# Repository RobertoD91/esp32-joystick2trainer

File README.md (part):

# esp32-joystick2trainer

> ⚠️ **AI-generated code.** This project (firmware, tests, CI and documentation) was written by
> an AI model, **Claude Fable 5.1** running in Claude Code, from a human specification and with
> human review and bench testing. Read the code before trusting it with anything that flies, and
> report anything odd in the issues.

*Click the image to watch the demo on YouTube.*

Firmware for the **ESP32-S3** that turns a wired **USB HID joystick** into a trainer input for
**EdgeTX** radios such as the **RadioMaster TX16S MKII**. The ESP32-S3 acts as a native USB host,
decodes the joystick's HID reports and emits **SBUS** and **CPPM** at the same time on two GPIOs.

```text
USB HID joystick  (e.g. Microsoft SideWinder Force Feedback 2, 045E:001B)
      │  USB full speed
      ▼
ESP32-S3 native USB host  ──►  HID report descriptor parser  ──►  normalised axes/buttons/hat
      │
      ▼
configurable channel mapping (source, invert, dead band, expo, end points, trim, failsafe)
      ├──►  SBUS  (UART1, 100000 8E2, hardware inverted)  ──►  GPIO 17
      └──►  CPPM  (RMT peripheral, no bit-banging)        ──►  GPIO 18
```

Force feedback is used for one thing: the bridge creates the **centring spring** on the joystick
(a USB HID PID effect; without it a SideWinder is loose) and offers a vibration test. Game-style
effects are out of scope.

> **Status:** flown. The firmware at commit `59b4e3c` (release v0.9.0 plus documentation
> updates) was used for a **first real flight on 2026-10-24** with a SideWinder Force Feedback 2,
> an ESP32-S3-DevKitC-1 and a RadioMaster TX16S MKII running EdgeTX, SBUS on the radio's AUX
> serial port (`Master/Serial`): it worked without issues. The CPPM output on the trainer jack
> and the SBUS input on the module bay S.PORT pin are implemented but **not yet tested on the
> radio**, and the force feedback added afterwards still needs its first bench test. See
> [Tested setups](#tested-setups).

## Contents

- [Features](#features)
- [Hardware](#hardware)
- [Wiring to the TX16S MKII](#wiring-to-the-tx16s-mkii)
- [EdgeTX setup](#edgetx-setup)
- [Building, flashing, testing](#building-flashing-testing)
- [Configuration](#configuration)
- [Architecture](#architecture)
- [Design decisions](#design-decisions)
- [Limitations and roadmap](#limitations-and-roadmap)

## Features

- **Native USB host** on the ESP32-S3 (ESP-IDF `usb` host library + Espressif `usb_host_hid`
  class driver). No Bluetooth, no external USB host shield.
- **Force feedback centring spring** for USB HID PID joysticks (SideWinder Force Feedback 2):
  the stick returns to centre by itself; strength and gain are configurable, plus a vibration
  test.
- **Generic HID joystick support**: the report descriptor is parsed at run time, so any joystick
  or gamepad that follows the HID usage tables works (X/Y/Z/Rx/Ry/Rz/slider/dial/wheel,
  throttle/rudder/accelerator/brake, hat switch, up to 32 buttons, report IDs, array buttons).
  The SideWinder Force Feedback 2 descriptor is part of the test suite.
- **SBUS and CPPM simultaneously**, each on its own GPIO, each individually configurable
  (period, polarity, number of channels, pulse width, frame length).
- **CPPM generated by the RMT peripheral**: the whole frame is handed to the hardware, timing does
  not depend on interrupt latency or on the USB task.
- **SBUS inversion in hardware** (UART TX inverter of the ESP32): no external transistor.
- **Safe disconnection handling**: on USB unplug the outputs go to a configurable failsafe
  (stop, hold, preset). By default they simply stop, which makes EdgeTX hand control back to
  the instructor's sticks within one second.
- **Everything configurable at run time** from a serial console and persisted in NVS:
  GPIOs, mapping per channel, inversion, dead band, expo, end points, trims, failsafe values,
  timings. Compile-time defaults are `-D` flags in `platformio.ini`.
- **PlatformIO project** with host-side unit tests (`pio test -e native`) and a GitHub Actions
  pipeline (format check, tests, firmware build with downloadable artifacts).

## Hardware

### Bill of materials

| Item | Notes |
|------|-------|
| ESP32-S3 dev board | Tested build target: `esp32-s3-devkitc-1`. Any ESP32-S3 board that exposes the **native USB** pins (GPIO19/20) works. Other chips: see [docs/hardware-options.md](docs/hardware-options.md) (short version: ESP32-S2 yes, RP2040/RP2350 and ESP32-C3/C5 no). |
| JR bay module (prototype PCB) | A 22 x 62 mm board that plugs into the radio's module bay: ESP32-S3-WROOM-1, USB-A host port, USB-C console, 2S buck, SBUS/CPPM on the bay pins and an AUX header. KiCad project, Gerbers, BOM and a printable case in [hardware/](hardware/README.md). Untested as of this release. |
| USB OTG cable **with power input** | Micro-USB (USB-C on some boards) OTG host plug + USB-A female for the joystick + a power input. See [Powering the joystick](#powering-the-joystick): a plain OTG adapter is not enough on the DevKitC-1. |
| USB-to-UART link | The DevKitC-1's second connector labelled "UART"; used for flashing, logs and the configuration console. |
| 3.5 mm TRS plug | For the CPPM trainer input of the radio. |
| Dupont wires / JR pins | For the SBUS input (module bay S.PORT pin or AUX serial connector). |

### Powering the joystick

The joystick must receive **5 V on VBUS** from the host connector, and the
**ESP32-S3-DevKitC-1 cannot provide it by design**: in the board schematic the VBUS pin of the
native "USB" connector (J4) reaches the 5 V rail only through the Schottky diode D7, oriented
from the connector *into* the board. The board can be powered from that port, but 5 V never
flows out to a connected device, and there is no jumper or solder pad to change that. The
firmware therefore enumerates nothing until VBUS is supplied in one of these ways:

1. **OTG Y-cable with power input** (no soldering, recommended): a "micro-USB OTG host + power"
   cable. Its power socket takes 5 V from a USB charger, its USB-A socket feeds the joystick, and
   the same 5 V also enters the board through D7, so one supply powers everything while the
   UART port stays free for the console.
2. **Wire from the header pin `5V` to the VBUS pad of J4**, or a solder bridge across D7. The
   board is then powered from the UART port or the `5V` pin. With D7 bridged, never connect a
   PC to the native port while the board is powered from another source.
3. **USB-A female breakout on the header**: VBUS to `5V`, GND to `GND`, D+ to `GPIO20`, D- to
   `GPIO19`, short twisted wires; the on-board connector is left unused.

The SideWinder FFB2 declares 100 mA over USB; it also has its own mains power supply for the
motors, which must be connected for the stick to enumerate reliably.

Power the ESP32 from its UART/USB connector or from a clean 5 V source. **Do not** power it from
the radio's module bay `BATT` pin: that pin carries the battery voltage (up to 8.4 V).

### GPIO usage (defaults)

| Signal | GPIO | Level | Change with |
|--------|------|-------|-------------|
| SBUS out | 17 | 3.3 V, idle low (inverted UART, standard SBUS) | `set sbus.gpio N`, `set sbus.inverted 0/1` |
| CPPM out | 18 | 3.3 V, idle high, 300 µs low pulses | `set cppm.gpio N`, `set cppm.inverted 0/1` |
| Status LED | none (-1) | active high | `set led.gpio N` |
| USB host D-/D+ | 19 / 20 | native USB | fixed |
| Console | UART0 (USB-UART bridge) | 115200 8N1 | fixed |

Avoid the strapping pins (0, 3, 45, 46), the flash/PSRAM pins (26-37 on modules with octal
PSRAM) and 19/20 (USB). 3.3 V logic is enough for the STM32 inputs of the TX16S (they are 5 V
tolerant, threshold about 2 V).

## Wiring to the TX16S MKII

EdgeTX offers several trainer input modes. The ones usable with this bridge on a TX16S are:

| EdgeTX trainer mode | Physical input on the TX16S | Signal to send | Bridge setting |
|---------------------|-----------------------------|----------------|----------------|
| **Master/Jack** | 3.5 mm trainer jack on the back | CPPM | `cppm.*` defaults |
| **Master/SBUS Module** | external module bay, **S.PORT** pin (with External RF **off**) | SBUS, standard polarity (idle low) | `sbus.inverted 1` (default) |
| **Master/Serial** | AUX1 (or AUX2) serial port configured as "SBUS Trainer" | SBUS, **UART polarity** (idle high) | `sbus.inverted 0` |
| Master/CPPM Module | module bay HEARTBEAT pin | – | **does not work on the TX16S/MKII** (hardware issue, EdgeTX issue #4672) |

EdgeTX uses one trainer mode per model, so in practice you connect **either** the CPPM output
**or** the SBUS output to the radio. Both are generated all the time; the other one is free for a
second radio or a simulator dongle.

### Tested setups

| Path | Radio side | Bridge side | Result |
|------|-----------|-------------|--------|
| **SBUS on AUX serial port** | TX16S MKII, EdgeTX, AUX port on the bottom set to `SBUS Trainer`, model in `Master/Serial`; external bay occupied by an ExpressLRS module, internal multi-protocol module | GPIO17 → AUX RX, GND → GND, **`set sbus.inverted 0`** + `save` | **Works, flown.** Bench-verified on 2026-09-20, first flight on 2026-10-24 with the firmware of commit `59b4e3c`: the model was flown from the joystick through the trainer function without any issue. |
| CPPM on the trainer jack | `Master/Jack` | GPIO18 → tip, GND → sleeve | Not yet tested (no jack at hand). Encoder timing is covered by unit tests against EdgeTX's decoder rules. |
| SBUS on module bay S.PORT | `Master/SBUS Module`, External RF off | GPIO17 → pin 5, `sbus.inverted 1` | Not yet tested (bay occupied by the ELRS module). |
| Force feedback (centring spring) | – | SideWinder FFB2 with its mains adapter connected | Implemented after the first flight, **not yet bench-tested**: the report sequence is verified against the real descriptor in the unit tests only. See [Force feedback](#force-feedback). |

Lessons learned during the first bring-up:

- The DevKitC-1 does not power the joystick from its native USB port; a powered OTG Y-cable
  fixed it (see [Powering the joystick](#powering-the-joystick)).
- The **AUX port wants UART polarity**: with the default `sbus.inverted 1` the radio sees
  nothing at all. `set sbus.inverted 0` takes effect immediately, then `save`.
- With the default `failsafe.mode stop` nothing is emitted until the joystick sends its first
  report; the SideWinder only reports on change, so move the stick once and check `status`.

### CPPM on the trainer jack (not yet verified on the radio)

```text
ESP32-S3 GPIO18 ──────► tip    (PPM)      3.5 mm TRS plug
ESP32-S3 GND    ──────► sleeve (GND)
                        ring   not connected
```

This follows the OpenTX/EdgeTX convention (PPM on the tip, ground on the sleeve, ring unused).
The original TX16S used a 4-pole socket, the MKII a standard 3-pole TRS socket. If your radio
does not see the signal, verify the socket with a multimeter (sleeve = ground) before assuming
a firmware problem. EdgeTX measures rising edge to rising edge, accepts 800-2200 µs per channel
and needs a sync gap of 4-19 ms; the encoder keeps every frame inside that window by design.

### SBUS on the module bay (S.PORT pin)

```text
JR module bay (top to bottom):  1 PPM   2 HEARTBEAT   3 BATT   4 GND   5 S.PORT
ESP32-S3 GPIO17 ──────► pin 5 (S.PORT)
ESP32-S3 GND    ──────► pin 4 (GND)
```

Keep `sbus.inverted = 1` (standard SBUS). Set the model's External RF to **OFF** or the mode is
not offered. Never connect pin 3 (BATT) to the ESP32.

### SBUS on the AUX serial port (verified)

```text
ESP32-S3 GPIO17 ──────► AUX port RX pin (the radio's receive line)
ESP32-S3 GND    ──────► AUX port GND
                        AUX port 5V and TX left unconnected
```

Set **`sbus.inverted = 0`** (the STM32F4 in the TX16S cannot invert its UART input, so the AUX
port expects idle-high UART polarity) and `save`. Do not exceed 3.3 V on the AUX pins. This path
works with any module in the external bay (it was verified with an ExpressLRS module installed).
See [docs/edgetx-tx16s.md](docs/edgetx-tx16s.md) for the EdgeTX serial-port settings.

## EdgeTX setup

1. **Radio Settings → Hardware** (only for the AUX variant): Serial ports → the AUX port you
   wired (AUX1 or AUX2) → `SBUS Trainer`.
2. **Model Settings → Trainer → Mode**: `Master/Jack` (CPPM), `Master/SBUS Module` or
   `Master/Serial`.
3. **Radio Settings → Trainer**: for each stick choose the mode (`Add` or `Replace`), the source
   channel (`CH1`…) and the weight. With the bridge connected and the joystick centred press
   **Cal** so that 1500 µs (SBUS 992) is the centre. Full travel is ±500 µs (SBUS 172…1811).
4. **Special Function**: add `Trainer` on a switch (for example `SH↓`) to enable stick takeover
   with that switch. When the switch is off, or when the trainer signal disappears, the radio's
   own sticks are used.
5. The trainer channels are also available as sources `TR1…TR16` in Inputs and Mixes, useful for
   buttons and the hat switch (default channels 5-14).

Default channel order (AETR + buttons), see [docs/configuration.md](docs/configuration.md):

| Channel | Source | Notes |
|---------|--------|-------|
| 1 | X (aileron) | |
| 2 | Y (elevator), inverted | forward = high |
| 3 | Slider (throttle), inverted | lever forward = high; failsafe = 1000 µs |
| 4 | Rz (twist, rudder) | |
| 5, 6 | buttons 1, 2 | trigger, thumb |
| 7, 8 | hat left/right, hat up/down | |
| 9-14 | buttons 3-8 | |
| 15, 16 | unassigned | 1500 µs |

## Building, flashing, testing

Requirements: [PlatformIO Core](https://docs.platformio.org/en/latest/core/installation/index.html)
(`pip install platformio`). The first build downloads the ESP-IDF 6.x toolchain (about 1.5 GB)
and the `espressif/usb` + `espressif/usb_host_hid` components from the ESP component registry.

```bash
pio run -e esp32s3                       # build the firmware
pio run -e esp32s3 -t upload             # flash through the UART connector
pio device monitor -b 115200             # logs + configuration console
pio test -e native                       # hardware independent unit tests (host)
```

CI builds every push and publishes `firmware.bin`, `bootloader.bin` and `partitions.bin` as a
workflow artifact; they can be flashed with `esptool.py` (offsets 0x0, 0x8000, 0x10000).

### Flash from the browser

No toolchain needed: open **https://robertodisanto.it/esp32-joystick2trainer/** in Chrome or
Edge, connect the board's UART port and click *Connect* (the page must be loaded over HTTPS,
Web Serial is not available on plain HTTP). The page (source in `web/`) is
redeployed by CI from `main` only after the format check, the unit tests and the firmware build
have passed, so it always serves a firmware that went through the whole pipeline.

## Configuration

Open the console (`pio device monitor` or any terminal at 115200 baud on the UART port) and type
`help`. The main commands:

| Command | Description |
|---------|-------------|
| `status` | joystick, outputs, current channel values |
| `hid` | parsed report descriptor and axis bindings of the connected joystick |
| `monitor [s]` | live axes/buttons/channels for a few seconds |
| `show [prefix]` | all configuration keys, or those starting with a prefix (`show ch3.`) |
| `set <key> <value>` | change a key in RAM |
| `save` / `load` / `defaults` | persist to NVS / reload / factory reset |
| `reboot` | restart (needed after changing GPIOs or enabling/disabling an output) |

Examples:

```text
set ch4.src axis:rz        # channel 4 follows the twist axis
set ch4.invert 1
set ch4.deadband 5         # 5 % dead band around the centre
set ch3.src axis:slider
set ch3.expo 30
set ch9.src btn:3
set ch9.toggle 1           # button 3 toggles channel 9
set cppm.channels 8
set sbus.inverted 0        # SBUS for the AUX port (UART polarity)
set failsafe.mode stop
save
```

The complete key reference is in [docs/configuration.md](docs/configuration.md).

## Force feedback

A SideWinder Force Feedback 2 has no mechanical spring: the centring force is a *software
effect* that the USB host has to create through the HID **PID** (Physical Interface Device)
protocol, which is why the stick feels loose on a host that does not speak PID. The bridge now
does what Windows and Linux do:

1. On connection it parses the PID output/feature reports from the descriptor (the same parser
   used for the joystick input), resets the device, enables the actuators and sets the device
   gain.
2. It creates a **spring** effect (Create New Effect → Block Load), uploads its parameters
   (Set Effect with infinite duration, Set Condition for both axes with the configured
   strength) and starts it. The stick then returns to centre by itself.
3. `ffb test [ms]` plays a sine **vibration** for a moment: a quick way to check that the
   actuators and the power supply are alive.

| Key / command | Default | Meaning |
|---------------|---------|---------|
| `ffb.enabled` | 1 | master switch; 0 stops the spring and zeroes the device gain |
| `ffb.spring` | 60 | spring strength 0..100 % (0 = no spring, the stick stays loose) |
| `ffb.gain` | 100 | overall device gain 0..100 % |
| `ffb.deadband` | 0 | zone around the centre without spring force, 0..50 % |
| `ffb.direction` | 0 | encoding of the spring's Set Effect: 0 = per-axis form of the PID specification (Axes Enable X+Y, one condition block per axis), 1 = the Linux `hid-pidff` form (Direction Enable, direction north). Flip to 1 if the stick centres on one axis only |
| `ffb` | – | console: PID status, transport in use, effect memory, actuator power, last error |
| `ffb test [ms]` | 600 ms | console: vibration test |

`set ffb.*` keys apply immediately (and persist with `save`). Output reports travel over the
joystick's interrupt OUT endpoint when it has one (the SideWinder does); if a transfer fails the
driver recovers the endpoint and the report is retried over control-pipe SET_REPORT, which then
stays in use for that connection. This needed a small addition to Espressif's HID host driver,
kept as a vendored copy in `components/usb_host_hid` (see its `NOTICE.md`).

Requirements and caveats:

- The SideWinder's **mains adapter must be connected**, otherwise the device reports
  "actuator power off" (visible in `ffb`) and no force is produced.
- Everything is generic PID, but only the SideWinder FFB2 descriptor has been exercised, and
  only in unit tests so far: the first bench test is pending. If the spring does not engage,
  `ffb` prints the step that failed.
- Devices with proprietary force-feedback protocols (older Logitech wheels and sticks, Xbox
  controllers) are not PID and are not supported.

## Device support and the "universal database" question

The firmware is already *descriptor driven*: any joystick, gamepad or wheel that is a standard
USB HID device is decoded from its own report descriptor, which is the same mechanism Windows
and Linux use. There is no central "joystick database" in Linux for HID devices because none is
needed; what Linux carries is a short list of per-device **quirks** (`drivers/hid/hid-quirks.c`,
`hid-ids.h`) plus dedicated drivers for non-HID controllers. For this project that translates
into three categories:

| Device class | Examples | Status |
|--------------|----------|--------|
| USB HID joystick/gamepad (report protocol) | SideWinder FFB2, Thrustmaster T.16000M, Logitech Extreme 3D Pro, PlayStation 4/5 controllers (wired), most generic gamepads | **Supported** by the generic parser; mapping adjusted with `set chN.src …` |
| USB HID with PID force feedback | SideWinder FFB2, Logitech MOMO/Driving Force (PID mode), Thrustmaster T.Flight/Hotas FFB | Spring/vibration supported through the generic PID client |
| Non-HID vendor protocols | Xbox 360/One/Series controllers (XInput/GIP), some Logitech "classic" FF devices | **Not supported**: they need dedicated vendor drivers (the way `USB_to_RC` handles XInput) |

What a database *can* add is semantics, not decoding: the
[SDL game controller DB](https://github.com/mdqinc/SDL_GameControllerDB) maps each known gamepad
(keyed by vendor/product) to a standard layout (left stick, A/B/X/Y, triggers), which is what
"universal" means for gamepads. Its text file is about 610 kB (46 kB compressed); it would fit
the 8 MB flash but needs the GUID matching logic, uses per-operating-system axis indices rather
than HID usages, and brings nothing for joysticks like the SideWinder, the Extreme 3D Pro or any
HOTAS, which it does not cover. The planned, lighter alternative is a small built-in **profile
table keyed on VID:PID** that preselects a sensible channel mapping and inversions per device
(the current defaults are, in effect, the SideWinder profile), with the generic parser as the
fallback for everything else. The full assessment, with a compatibility table built from the
Linux driver sources and a roadmap, is in [docs/device-support.md](docs/device-support.md).

## Architecture

```text
lib/rc_core     pure C++17, no hardware:  SBUS encoder, CPPM waveform encoder, RMT symbol
                packer, channel mapper, configuration model + key/value interface
lib/hid_core    pure C++17, no hardware:  HID report descriptor parser (input/output/feature),
                                          joystick decoder, bit-field codec, PID force-feedback
                                          client (report builders + controller sequences)
components/     usb_host_hid: vendored Espressif HID host driver + interrupt OUT endpoint API
src/app         ESP-IDF layer:            UsbJoystick (usb host + hid driver), InputHub,
                                          SbusOutput (UART), CppmOutput (RMT), FfbController
                                          (PID over USB), ConfigStore (NVS), console, StatusLed
src/main.cpp    wiring of the above
test/           Unity tests for lib/ (run on the host, `pio test -e native`)
```

Tasks at run time:

| Task | Core | Role |
|------|------|------|
| `usb_lib` | 0 | USB host library daemon |
| HID driver task | 0 | USB transfers, calls back with raw reports |
| `hid_evt` | 0 | opens new devices, fetches/parses the report descriptor |
| `ffb` | 0 | PID force feedback: spring upload on connect, config changes, vibration test |
| `sbus` | 1 | one frame every `sbus.period` µs (esp_timer driven) |
| `cppm` | 1 | keeps two frames queued in the RMT hardware |
| console REPL | any | configuration commands |

Decoded reports are mapped to channels on the USB task and stored in the `InputHub`; the output
tasks only read the latest frame and apply the failsafe policy. Disconnection is detected by the
USB host stack (port disconnect), not by a data timeout, because many joysticks only send a
report when something changes. An optional data timeout exists (`input.timeout`) for devices
known to stream continuously.

## Design decisions

The full evaluation of the existing projects is in [docs/research.md](docs/research.md). In short:

- **ESP-IDF instead of Arduino.** The official PlatformIO `espressif32` platform ships Arduino
  core 2.x (IDF 4.4) for the S3, which lacks the current USB host stack; the community
  `pioarduino` platform fixes that but adds an unofficial dependency. Pure ESP-IDF 6.x gives the
  USB host library, the `usb_host_hid` class driver, the RMT TX driver, UART inversion,
  `esp_console` and NVS directly, with the official PlatformIO platform.
- **Espressif's `usb_host_hid` driver** instead of `EspUsbHost` (Arduino-only, very large,
  unstable API). It started as a registry dependency; since force feedback needs the interrupt
  OUT endpoint, which the upstream driver ignores, it is now a vendored copy with a small,
  clearly marked addition (`components/usb_host_hid/NOTICE.md`). The `usb` host library itself
  still comes from the registry.
- **Own HID descriptor parser and joystick decoder** (about 500 lines, allocation-free, unit
  tested with the real SideWinder descriptor) instead of per-device hard-coded report layouts
  keyed on report length, which is what every ESP32 joystick example found does.
- **Own SBUS and CPPM encoders**: they are tiny, they must be testable on the host, and the
  Arduino-oriented libraries (`bolderflight/sbus`, `DiyMotionController`) would only add a
  `Serial`/timer-ISR dependency. CPPM on the RMT peripheral is unique to this project; every
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
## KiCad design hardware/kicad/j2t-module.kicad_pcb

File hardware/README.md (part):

# JR bay module: prototype PCB

A 22 x 62 mm two-layer board that turns the firmware into a module for the external
module bay of an EdgeTX radio (TX16S and similar). It carries an ESP32-S3-WROOM-1, a USB-A
host port for the joystick, a USB-C console/flashing port, a 2S-to-5 V buck converter
and the bay connector. Everything in this directory was generated from one Python
description (`scripts/design.py`) with KiCad 7: schematic, PCB, routing, fabrication
outputs, BOM and the printable case.

**Status: designed, not built.** No board of this revision has been manufactured or
powered yet. Read "Before ordering" below.

Licence: the hardware design files in this directory are released under the
CERN Open Hardware Licence Version 2, Permissive (`LICENSE`, SPDX `CERN-OHL-P-2.0`).
The firmware keeps the project's licence.

## What is on the board

| Block | Parts | Notes |
|---|---|---|
| MCU | U3 ESP32-S3-WROOM-1-N8 | Same target as the firmware (`esp32s3` / `esp32s3-module` environments). Mounted on the radio side; its antenna area is unused and sits over copper (no Wi-Fi/BLE intended). |
| USB host | J1 USB-A receptacle, D2 ESD array, Q5/Q6 VBUS switch, F2 0.75 A polyfuse, C8/C9 2 x 47 uF | GPIO19/20 native USB. GPIO2 can switch the joystick's VBUS off (pulled up: on by default, no firmware support needed). |
| Console / flashing | J2 USB-C, U4 CH340C, Q7/Q8 auto-reset, SW1 RESET, SW2 BOOT | UART0 (TXD0/RXD0). Auto-reset works like on a dev board: `pio run -t upload` with no button presses. |
| Bay supply | F1 1.1 A polyfuse, Q1 reverse-polarity P-FET, U1 TPS54202 buck, L1 10 uH, C1/C2 input, C5/C7 output | 2S input (6.0 to 8.4 V) from the bay's VBAT pin to 5 V, up to about 1.5 A. Q1's gate rating limits the input to 2S packs. |
| Bench supply | D7 Schottky | USB-C 5 V is ORed into the 5 V rail: about 4.5 V on the rail when only the cable is plugged, enough for flashing and for the joystick on the bench. The buck has priority when the bay supply is present. |
| 3.3 V | U2 AP2112K-3.3 | 600 mA LDO from the 5 V rail. |
| Outputs | R16/R18 series resistors, JP1/JP2 solder jumpers, J5 bay header | SBUS on the bay's S.PORT pin, CPPM on the heartbeat pin, 1 k in series. |
| AUX | J3 1x3 header (GND, SBUS, CPPM) | For the radio's AUX serial port, or a cable to a 3.5 mm plug for the trainer jack. The on-board jack was dropped: a jack needs 10 mm of width plus locating pegs that would sit under the module. |
| Display | J4 1x4 1.27 mm pins (GND, 3V3, SCL, SDA), R26/R27 pull-ups | GPIO9 (SCL) and GPIO10 (SDA) for the I2C display described in `docs/hardware-options.md`. Not used by the firmware yet. |
| Sensing | R22/R23/C16 | Battery voltage on GPIO1 (ADC), 8.4 V -> 1.5 V. Not used by the firmware yet. |
| Indicators | D5 green status LED (GPIO38), D6 red 3.3 V LED | `led.gpio 38` is the default of the `esp32s3-module` environment. |
| Spare input | R21 | The bay's PPM pin into GPIO16 (future use). |

### Firmware pins

| Function | GPIO | Firmware key / build flag |
|---|---|---|
| SBUS out (bay S.PORT, AUX) | 17 | `sbus.gpio`, `-DJ2T_SBUS_GPIO` |
| CPPM out (bay heartbeat, AUX) | 18 | `cppm.gpio`, `-DJ2T_CPPM_GPIO` |
| Status LED | 38 | `led.gpio`, `-DJ2T_LED_GPIO=38` (set by `esp32s3-module`) |
| USB host D-/D+ | 19 / 20 | fixed |
| Console UART | TXD0 / RXD0 | fixed |
| Joystick VBUS enable (active high, pulled up) | 2 | not used yet |
| I2C SCL / SDA | 9 / 10 | not used yet |
| Battery sense (ADC) | 1 | not used yet |
| Bay PPM in | 16 | not used yet |
| BOOT button | 0 | strapping pin, as on a dev board |

Build the firmware for the module with `pio run -e esp32s3-module -t upload`.

### Bay connector and jumpers

The 5-pin header J5 follows the usual JR bay order as seen on the module:

| Pin | Signal | On the board |
|---|---|---|
| 1 | PPM | R21 -> GPIO16 (input, spare) |
| 2 | heartbeat | JP1: centre pad to GND (pad 1) or to the CPPM output (pad 3) |
| 3 | VBAT | fuse, reverse protection, buck |
| 4 | GND | JP2: centre pad to GND (pad 1) or to the CPPM output (pad 3) |
| 5 | S.PORT | R16 <- GPIO17 SBUS |

Both jumpers are open as shipped. **Measure the bay before bridging anything**: with the
radio on, the pin with battery voltage is VBAT and the one at 0 V next to it is GND. For
the standard order bridge JP2 1-2 (pin 4 = GND) and JP1 2-3 (pin 2 = CPPM). If the order is
mirrored on your radio, bridge JP1 1-2 and JP2 2-3 instead; S.PORT and PPM are both driven
through 1 k resistors, so a mirrored order is harmless and only needs `sbus.gpio` changed.
Do not bridge both jumpers to the same function.

## Files

| Path | Content |
|---|---|
| `kicad/j2t-module.kicad_pro`, `.kicad_sch`, `.kicad_pcb` | KiCad 7 project. The schematic embeds its symbols and the board embeds its footprints, so no extra libraries are needed. |
| `kicad/j2t-module.net` | Netlist exported from the schematic; `scripts/check_netlist.py` verifies it against `design.py` (44 nets, 0 mismatches). |
| `kicad/j2t-module-drc-report.txt` | DRC of the delivered board: 0 unconnected items, 0 clearance or courtyard errors; the remaining entries are "silkscreen clipped by board edge" warnings from the connector bodies and "footprint differs from library" notes (the WROOM courtyard was trimmed). |
| `fab/j2t-module-gerbers.zip` | Gerber X2 (F/B copper, paste, mask, silkscreen, fab, edge cuts) and Excellon drill files (PTH and NPTH separate, with maps). |
| `fab/j2t-module-pos.csv` | Pick and place, both sides, millimetres, KiCad conventions (Y grows upwards, origin at the sheet origin). |
| `fab/j2t-module-bom.csv` | BOM grouped by value and package with manufacturer part numbers where it matters. |
| `fab/*.pdf` | Schematic, component side and radio side (mirrored) drawings. |
| `case/case.scad`, `case/*.stl` | Parametric sleeve case, standard JR and lite variants (see "Case"). |
| `scripts/` | The generator: `design.py` (parts, nets, placement regions), `sch_gen.py`, `pcb_gen.py` + `router.py` (placement, routing, zones, DRC), `postprocess.py`, `bom.py`, `check_netlist.py`, `sexp.py`. |

## Board facts

- 22.0 x 62.0 mm, 1.6 mm FR-4, two copper layers, 1 oz, rounded corners (r 1 mm).
- Design rules used: 0.2 mm clearance, 0.2 mm signal / 0.5 mm power tracks (0.4 mm on the
  USB-C VBUS loop), vias 0.6 mm / 0.3 mm drill, 0.3 mm copper-to-edge, ground pours on
  both sides with solid pad connections. Any standard 2-layer service covers this
  (PCBWay standard: 2 layers, 1.6 mm, HASL or ENIG, green mask, white silk).
- Component side ("F", towards the pilot): USB-A at the top end, USB-C on the left edge,
  CH340C, buttons, LEDs, output resistors, jumpers, AUX header and I2C pins.
- Radio side ("B"): ESP32 module with its open (antenna) end towards the USB connectors,
  buck converter at the top end, ESD arrays and VBUS capacitors under the USB-A.
- Smallest parts: 0402 passives, SOT-323 transistors, 0.5 mm pitch USB-C pads. Meant for
  reflow (stencil files are in the Gerber set); hand soldering is possible with a fine tip
  and flux, except for the USB-C receptacle which wants hot air.
- 63 parts, 41 BOM lines. Manufacturer part numbers are given where a specific part is
  needed (regulators, FETs, ESD arrays, inductor, fuses, switches, connectors); the
  passives are generic 0402/0805/1210 X5R/X7R parts.

## Before ordering

Things that the design assumes and that a bench or a ruler should confirm first.

1. **Bay dimensions.** The width of 22 mm and the length of 62 mm were chosen from the
   published sizes of lite modules, not from a measured TX16S. Measure on the radio: cavity
   width, thickness (depth from the back face to the inner wall) and length, the position
   of the 5-pin socket relative to the cavity walls and its depth, and which way the
   module's back face points. Compare with the case parameters (`outer_w`, `outer_t`,
   `pcb_l + end_wall + lip`) and with the header position on the board (pins centred at
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
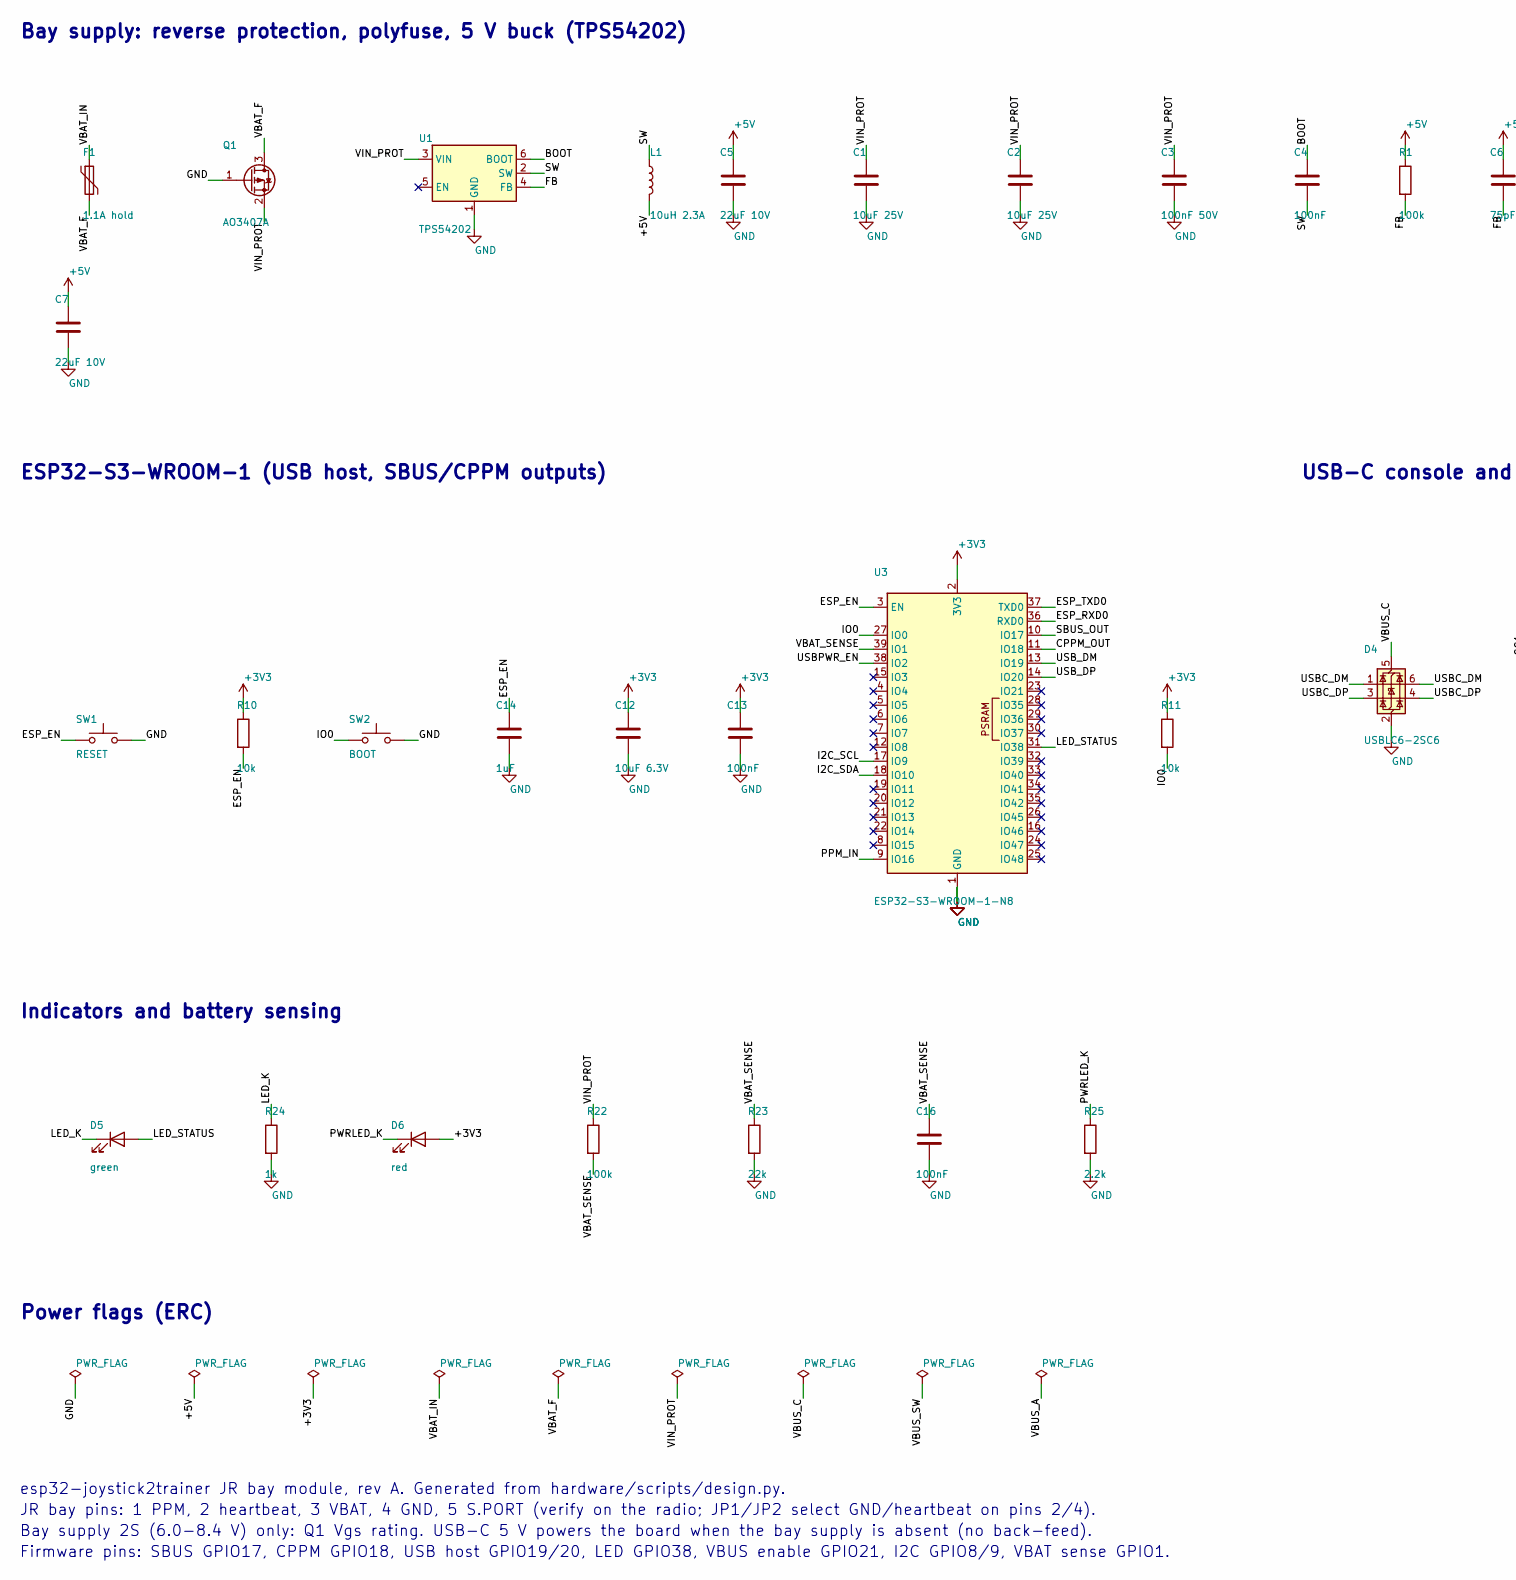
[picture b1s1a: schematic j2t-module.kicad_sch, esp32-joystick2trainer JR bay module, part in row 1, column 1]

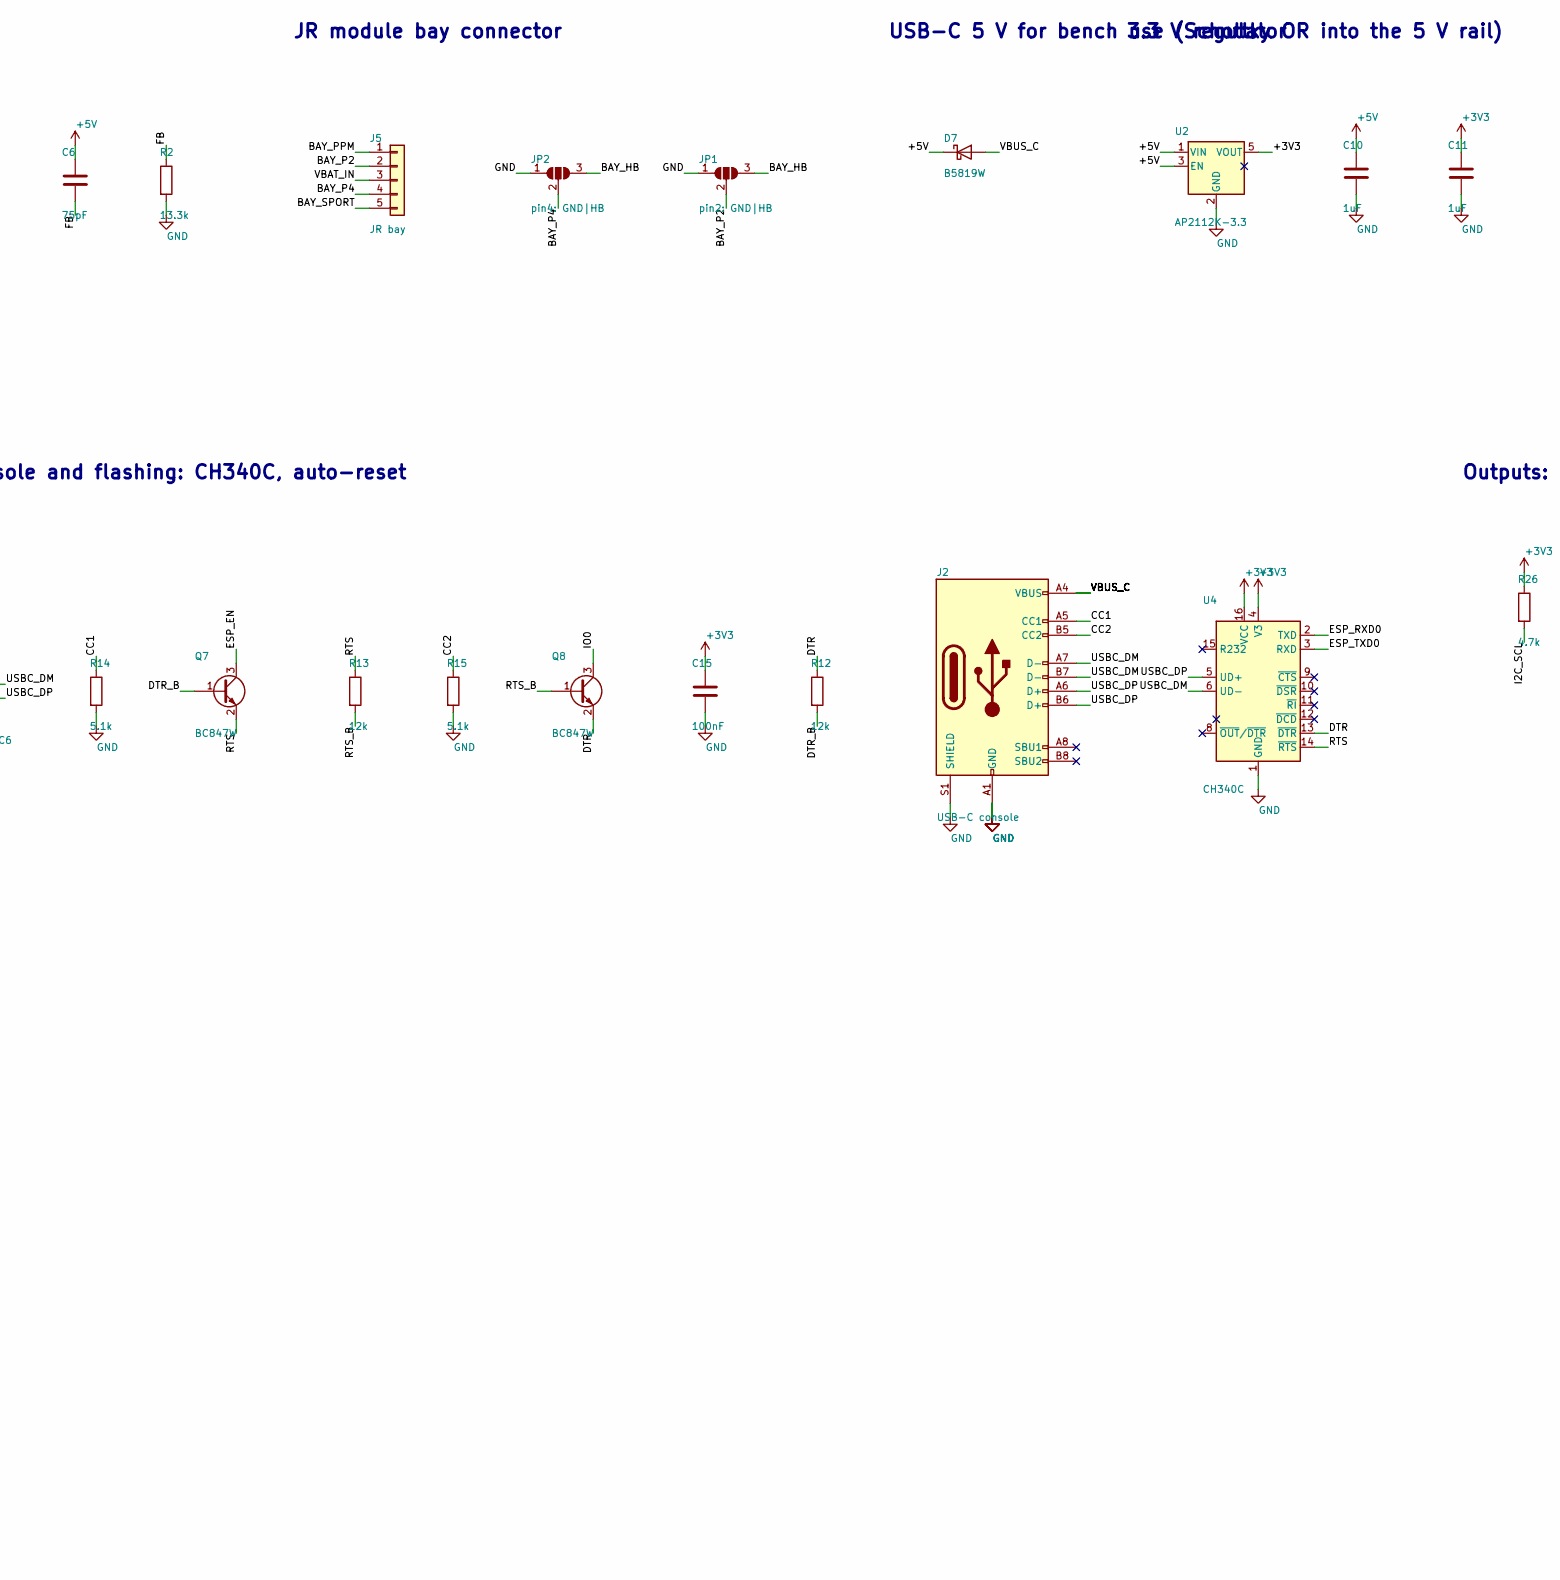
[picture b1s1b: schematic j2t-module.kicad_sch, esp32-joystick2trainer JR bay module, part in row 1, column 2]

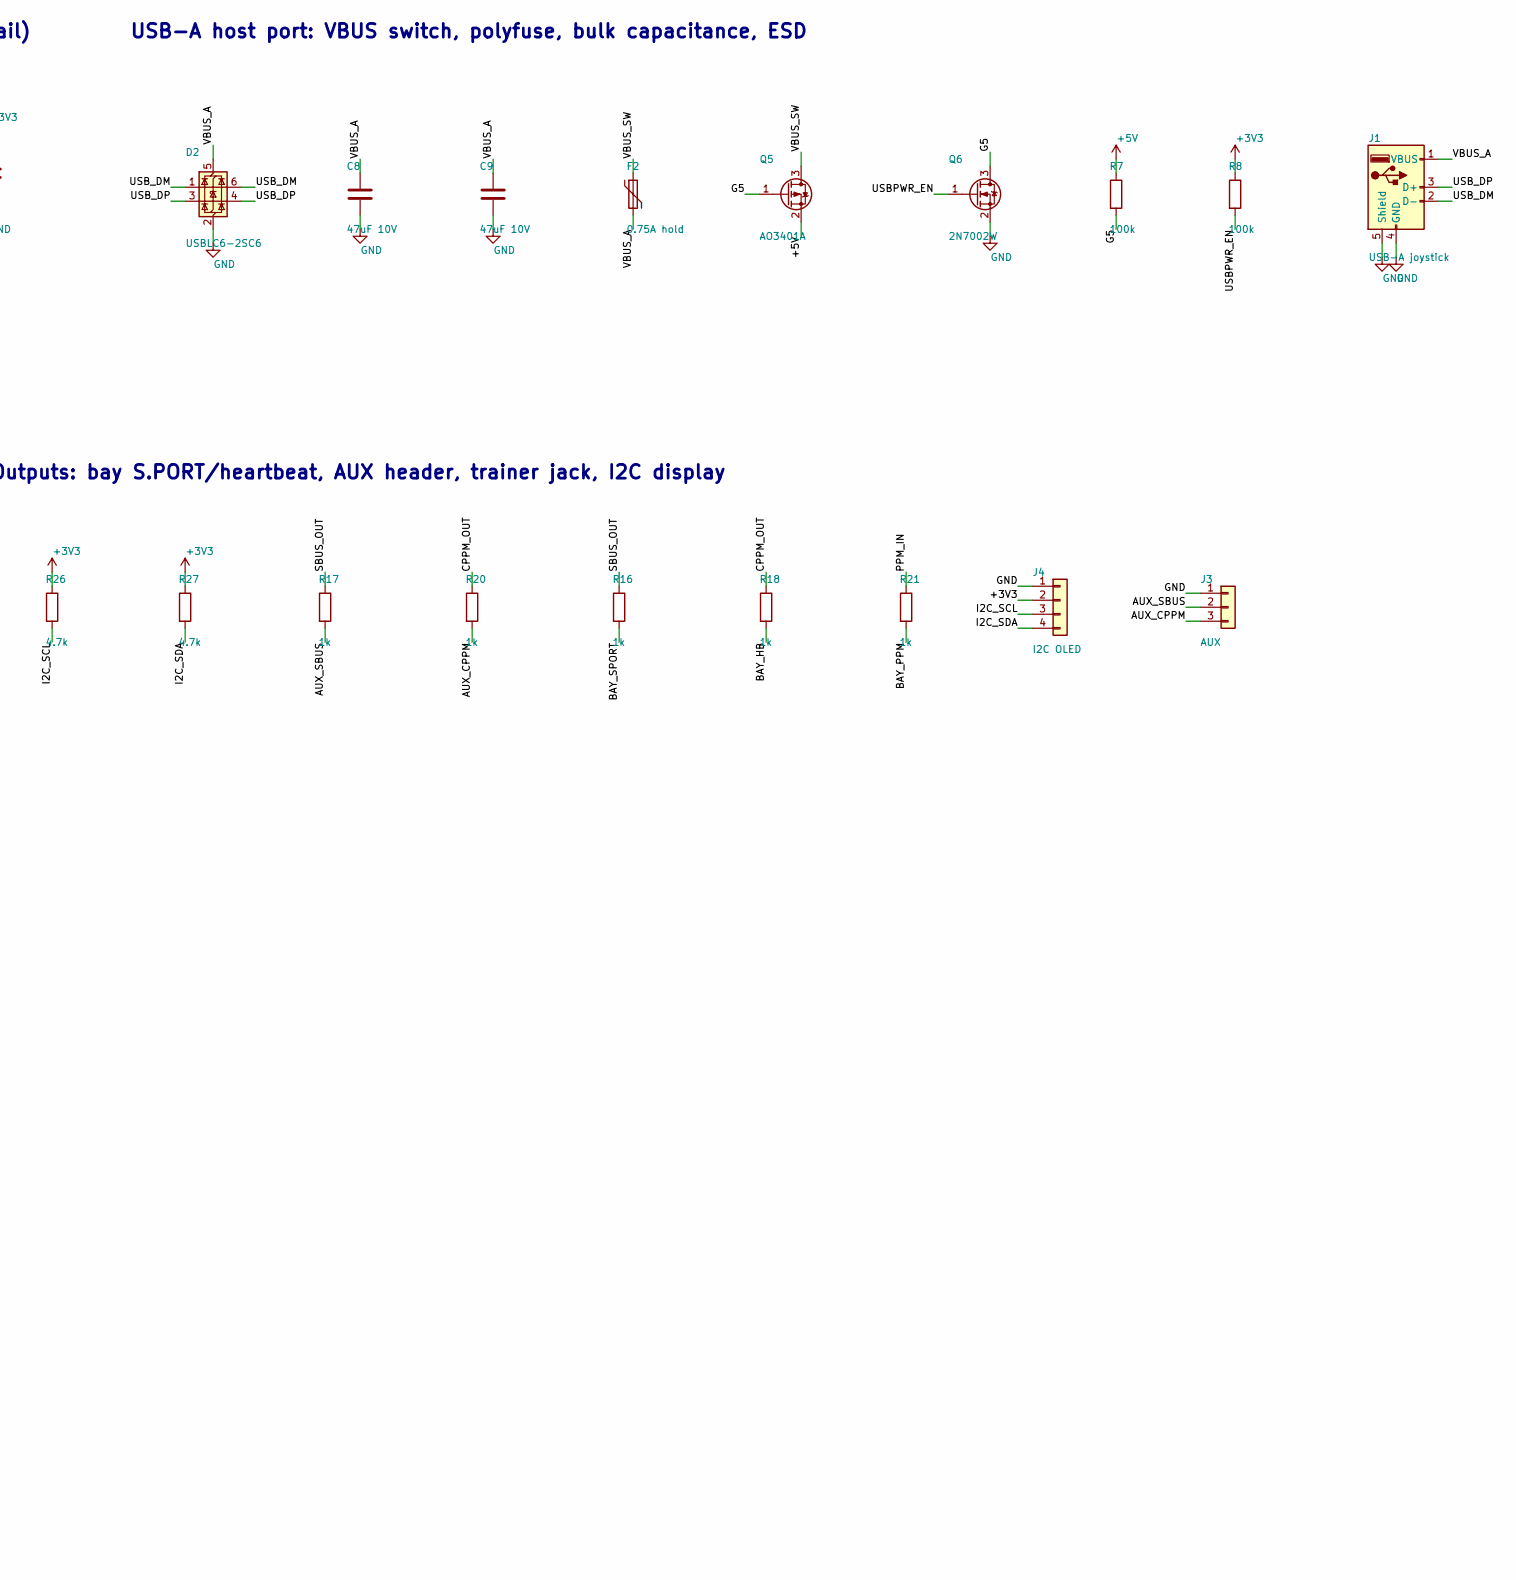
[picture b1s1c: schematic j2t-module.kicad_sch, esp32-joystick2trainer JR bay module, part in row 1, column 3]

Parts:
C1, C2: 10uF 25V; C_0805_2012Metric
C3: 100nF 50V; C_0402_1005Metric
C4, C13, C15, C16: 100nF; C_0402_1005Metric
C5, C7: 22uF 10V; C_0805_2012Metric
C6: 75pF; C_0402_1005Metric
C8, C9: 47uF 10V; C_1210_3225Metric
C10, C11, C14: 1uF; C_0402_1005Metric
C12: 10uF 6.3V; C_0402_1005Metric
D2, D4: USBLC6-2SC6; SOT-23-6; MPN USBLC6-2SC6
D5: green; LED_0603_1608Metric
D6: red; LED_0603_1608Metric
D7: B5819W; D_SOD-123; MPN B5819W
F1: 1.1A hold; Fuse_1206_3216Metric; MPN 1206L110
F2: 0.75A hold; Fuse_1206_3216Metric; MPN 1206L075
J1: USB-A joystick; USB_A_Molex_67643_Horizontal; MPN Molex 67643-0910 or equivalent right-an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
J2: USB-C console; USB_C_Receptacle_HRO_TYPE-C-31-M-12; MPN HRO TYPE-C-31-M-12
J3: AUX; PinHeader_1x03_P2.54mm_Vertical_SMD_Pin1Left
J4: I2C OLED; PinHeader_1x04_P1.27mm_Vertical; MPN 1.27 mm pitch 1x4 pin header (or solder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
J5: JR bay; PinHeader_1x05_P2.54mm_Horizontal; MPN 2.54 mm right-angle header, long pins
JP1: pin2: GND|HB; SolderJumper-3_P1.3mm_Open_RoundedPad1.0x1.5mm
JP2: pin4: GND|HB; SolderJumper-3_P1.3mm_Open_RoundedPad1.0x1.5mm
L1: 10uH 2.3A; L_Sunlord_SWPA5040S; MPN SWPA5040S100MT
Q1: AO3407A; SOT-23; MPN AO3407A
Q5: AO3401A; SOT-23; MPN AO3401A
Q6: 2N7002W; SOT-323_SC-70; MPN 2N7002W
Q7, Q8: BC847W; SOT-323_SC-70; MPN BC847W
R1, R7, R8, R22: 100k; R_0402_1005Metric
R2: 13.3k; R_0402_1005Metric
R10, R11: 10k; R_0402_1005Metric
R12, R13: 12k; R_0402_1005Metric
R14, R15: 5.1k; R_0402_1005Metric
R16, R17, R18, R20, R21, R24: 1k; R_0402_1005Metric
R23: 22k; R_0402_1005Metric
R25: 2.2k; R_0402_1005Metric
R26, R27: 4.7k; R_0402_1005Metric
SW1: RESET; SW_Push_1P1T_NO_CK_KMR2; MPN KMR221GLFS
SW2: BOOT; SW_Push_1P1T_NO_CK_KMR2; MPN KMR221GLFS
U1: TPS54202; SOT-23-6; MPN TPS54202DDCR
U2: AP2112K-3.3; SOT-23-5; MPN AP2112K-3.3TRG1
U3: ESP32-S3-WROOM-1-N8; ESP32-S3-WROOM-1; MPN ESP32-S3-WROOM-1-N8
U4: CH340C; SOIC-16_3.9x9.9mm_P1.27mm; MPN CH340C

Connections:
AUX_CPPM: J3.3, R20.2
AUX_SBUS: J3.2, R17.2
BAY_HB: JP1.3 (B), JP2.3 (B), R18.2
BAY_P2: J5.2, JP1.2 (C)
BAY_P4: J5.4, JP2.2 (C)
BAY_PPM: J5.1, R21.2
BAY_SPORT: J5.5, R16.2
BOOT: C4.1, U1.6 (BOOT)
CC1: J2.A5 (CC1), R14.1
CC2: J2.B5 (CC2), R15.1
CPPM_OUT: R18.1, R20.1, U3.11 (IO18)
DTR: Q8.2 (E), R12.1, U4.13 (~DTR)
DTR_B: Q7.1 (B), R12.2
ESP_EN: C14.1, Q7.3 (C), R10.2, SW1.1, U3.3 (EN)
ESP_RXD0: U3.36 (RXD0), U4.2 (TXD)
ESP_TXD0: U3.37 (TXD0), U4.3 (RXD)
FB: C6.2, R1.2, R2.1, U1.4 (FB)
G5: Q5.1 (G), Q6.3 (D), R7.2
I2C_SCL: J4.3, R26.2, U3.17 (IO9)
I2C_SDA: J4.4, R27.2, U3.18 (IO10)
IO0: Q8.3 (C), R11.2, SW2.1, U3.27 (IO0)
LED_K: D5.1 (K), R24.1
LED_STATUS: D5.2 (A), U3.31 (IO38)
PPM_IN: R21.1, U3.9 (IO16)
PWRLED_K: D6.1 (K), R25.1
RTS: Q7.2 (E), R13.1, U4.14 (~RTS)
RTS_B: Q8.1 (B), R13.2
SBUS_OUT: R16.1, R17.1, U3.10 (IO17)
SW: C4.2, L1.1, U1.2 (SW)
USBC_DM: D4.1 (I/O1), D4.6 (I/O1), J2.A7 (D-), J2.B7 (D-), U4.6 (UD-)
USBC_DP: D4.3 (I/O2), D4.4 (I/O2), J2.A6 (D+), J2.B6 (D+), U4.5 (UD+)
USBPWR_EN: Q6.1 (G), R8.2, U3.38 (IO2)
USB_DM: D2.1 (I/O1), D2.6 (I/O1), J1.2 (D-), U3.13 (IO19)
USB_DP: D2.3 (I/O2), D2.4 (I/O2), J1.3 (D+), U3.14 (IO20)
VBAT_SENSE: C16.1, R22.2, R23.1, U3.39 (IO1)

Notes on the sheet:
Bay supply: reverse protection, polyfuse, 5 V buck (TPS54202)
JR module bay connector
USB-C 5 V for bench use (Schottky OR into the 5 V rail)
3.3 V regulator
USB-A host port: VBUS switch, polyfuse, bulk capacitance, ESD
ESP32-S3-WROOM-1 (USB host, SBUS/CPPM outputs)
USB-C console and flashing: CH340C, auto-reset
Outputs: bay S.PORT/heartbeat, AUX header, trainer jack, I2C display
Indicators and battery sensing
Power flags (ERC)
esp32-joystick2trainer JR bay module, rev A. Generated from hardware/scripts/design.py.
JR bay pins: 1 PPM, 2 heartbeat, 3 VBAT, 4 GND, 5 S.PORT (verify on the radio; JP1/JP2 select GND/heartbeat on pins 2/4).
Bay supply 2S (6.0-8.4 V) only: Q1 Vgs rating. USB-C 5 V powers the board when the bay supply is absent (no back-feed).
Firmware pins: SBUS GPIO17, CPPM GPIO18, USB host GPIO19/20, LED GPIO38, VBUS enable GPIO21, I2C GPIO8/9, VBAT sense GPIO1.

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
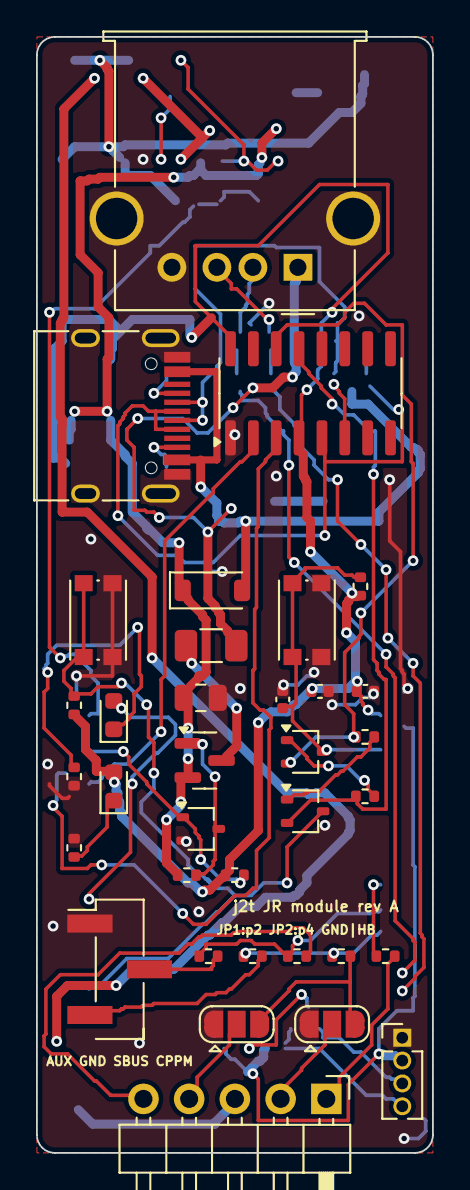
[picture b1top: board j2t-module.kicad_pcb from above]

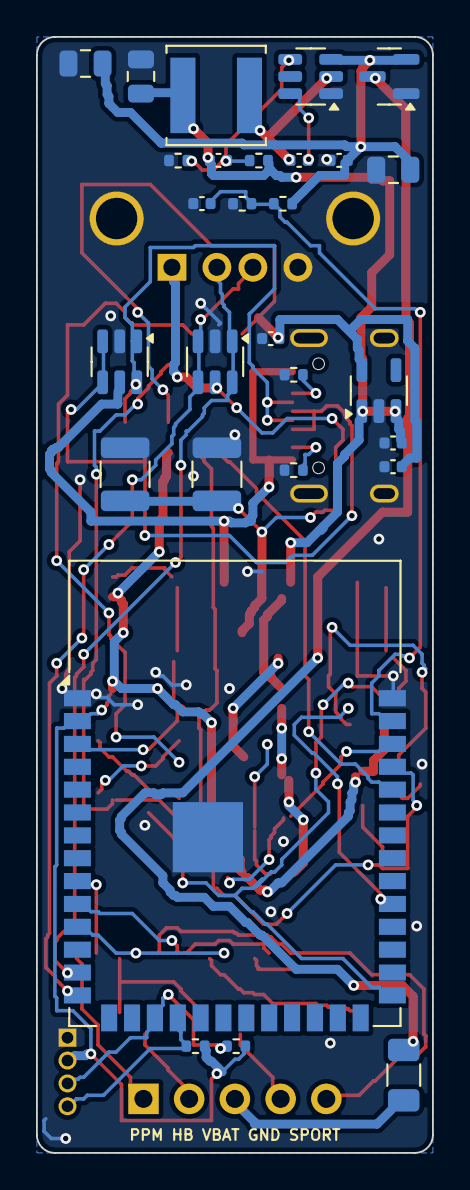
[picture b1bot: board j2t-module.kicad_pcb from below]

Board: 2 copper layers, 22.0 x 62.0 mm, 63 parts (28 on the bottom side), 44 nets.

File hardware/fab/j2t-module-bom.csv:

Designator,Qty,Value,Footprint,MPN,DNP,Note
"C1, C2",2,10uF 25V,C_0805_2012Metric,,,
"C10, C11, C14",3,1uF,C_0402_1005Metric,,,
C12,1,10uF 6.3V,C_0402_1005Metric,,,3V3 decoupling next to U3 pin 2
C3,1,100nF 50V,C_0402_1005Metric,,,
"C4, C13, C15, C16",4,100nF,C_0402_1005Metric,,,8.4 V -> 1.5 V on GPIO1 (ADC)
"C5, C7",2,22uF 10V,C_0805_2012Metric,,,C5 + C7 = 44 uF buck output capacitance (datasheet table 7-2); also the VBUS switch input reservoir
C6,1,75pF,C_0402_1005Metric,,,feed-forward across R1 (datasheet table 7-2)
"C8, C9",2,47uF 10V,C_1210_3225Metric,,,USB host port bulk capacitance (ceramic compromise for the 120 uF requirement)
"D2, D4",2,USBLC6-2SC6,SOT-23-6,USBLC6-2SC6,,"D+ and D- pads line up with the USB-A pins; rows: D+/GND/D- towards the USB-A, D+/VBUS/D- towards the module"
D5,1,green,LED_0603_1608Metric,,,status LED (led.gpio 38)
D6,1,red,LED_0603_1608Metric,,,3.3 V present
D7,1,B5819W,D_SOD-123,B5819W,,"USB-C 5 V ORed into the 5 V rail through a Schottky: reverse biased while the buck runs, about 4.5 V on the rail when only the USB-C is plugged (bench use)"
F1,1,1.1A hold,Fuse_1206_3216Metric,1206L110,,next to the bay header: the unfused net stays short
F2,1,0.75A hold,Fuse_1206_3216Metric,1206L075,,
J1,1,USB-A joystick,USB_A_Molex_67643_Horizontal,Molex 67643-0910 or equivalent right-angle USB-A receptacle,,
J2,1,USB-C console,USB_C_Receptacle_HRO_TYPE-C-31-M-12,HRO TYPE-C-31-M-12,,position keeps the 0.3 mm pads on the router's 0.1 mm grid
J3,1,AUX,PinHeader_1x03_P2.54mm_Vertical_SMD_Pin1Left,,,"GND / SBUS / CPPM: AUX serial port cable, or a cable to a 3.5 mm plug for the trainer jack; plugs from the back face"
J4,1,I2C OLED,PinHeader_1x04_P1.27mm_Vertical,1.27 mm pitch 1x4 pin header (or solder the display cable directly),,GND VCC SCL SDA for a 0.91in 128x32 SSD1306 module; pin 1 nearest the bay header
J5,1,JR bay,PinHeader_1x05_P2.54mm_Horizontal,"2.54 mm right-angle header, long pins",,"Pin 1 PPM, 2 heartbeat, 3 VBAT, 4 GND, 5 S.PORT: verify on the radio before bridging JP1/JP2"
JP1,1,pin2: GND|HB,SolderJumper-3_P1.3mm_Open_RoundedPad1.0x1.5mm,,,"bridge 2-3 (HB) when pin 2 is the heartbeat, 1-2 (GND) when the bay order is mirrored"
JP2,1,pin4: GND|HB,SolderJumper-3_P1.3mm_Open_RoundedPad1.0x1.5mm,,,"bridge 1-2 (GND) for the standard order, 2-3 (HB) when mirrored"
L1,1,10uH 2.3A,L_Sunlord_SWPA5040S,SWPA5040S100MT,,"5x5x4 mm; SWPA5030S100MT (3 mm high, 1.5 A sat) if the case is too thin"
Q1,1,AO3407A,SOT-23,AO3407A,,Reverse polarity protection (Vgs max 20 V: 2S battery packs only)
Q5,1,AO3401A,SOT-23,AO3401A,,"VBUS switch, on by default"
Q6,1,2N7002W,SOT-323_SC-70,2N7002W,,
"Q7, Q8",2,BC847W,SOT-323_SC-70,BC847W,,auto-reset: EN; auto-reset: IO0
"R1, R7, R8, R22",4,100k,R_0402_1005Metric,,,pull-up: joystick powered even before the firmware runs; GPIO2 low cuts VBUS
"R10, R11",2,10k,R_0402_1005Metric,,,
"R12, R13",2,12k,R_0402_1005Metric,,,
"R14, R15",2,5.1k,R_0402_1005Metric,,,
"R16, R17, R18, R20, R21, R24",6,1k,R_0402_1005Metric,,,radio PPM/CRSF output into a spare GPIO (future use)
R2,1,13.3k,R_0402_1005Metric,,,
R23,1,22k,R_0402_1005Metric,,,
R25,1,2.2k,R_0402_1005Metric,,,
"R26, R27",2,4.7k,R_0402_1005Metric,,,omit if the display module has its own pull-ups
SW1,1,RESET,SW_Push_1P1T_NO_CK_KMR2,KMR221GLFS,,
SW2,1,BOOT,SW_Push_1P1T_NO_CK_KMR2,KMR221GLFS,,
U1,1,TPS54202,SOT-23-6,TPS54202DDCR,,EN left floating = enabled (internal pull-up)
U2,1,AP2112K-3.3,SOT-23-5,AP2112K-3.3TRG1,,
U3,1,ESP32-S3-WROOM-1-N8,ESP32-S3-WROOM-1,ESP32-S3-WROOM-1-N8,,"8 MB flash, same as the firmware's esp32s3 target. Radio unused: antenna keep-out not applied."
U4,1,CH340C,SOIC-16_3.9x9.9mm_P1.27mm,CH340C,,"3.3 V operation: V3 tied to VCC. Pins 1-8 (UART, USB) on the row facing the module, 9-16 (DTR/RTS) facing the USB-A"

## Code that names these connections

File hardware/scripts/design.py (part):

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    note="USB-C 5 V ORed into the 5 V rail through a Schottky: reverse biased while the buck runs, "
         "about 4.5 V on the rail when only the USB-C is plugged (bench use)")
add("C8", "Device", "C", C1210, "47uF 10V", {"1": "VBUS_A", "2": "GND"}, "usb_a", region="B2a", rot=90)
add("C9", "Device", "C", C1210, "47uF 10V", {"1": "VBUS_A", "2": "GND"}, "usb_a", region="B2a", rot=90,
    note="USB host port bulk capacitance (ceramic compromise for the 120 uF requirement)")
add("F2", "Device", "Polyfuse", "Fuse:Fuse_1206_3216Metric", "0.75A hold", {"1": "VBUS_SW", "2": "VBUS_A"},
    "usb_a", region="T3", rot=0, mpn="1206L075")
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     "8": "NC_U4_8", "9": "NC_U4_9", "10": "NC_U4_10", "11": "NC_U4_11", "12": "NC_U4_12",
     "13": "DTR", "14": "RTS", "15": "NC_U4_15", "16": "+3V3"},
    "usb_c", x=15.2, y=19.8, rot=90, side="F", mpn="CH340C",
    note="3.3 V operation: V3 tied to VCC. Pins 1-8 (UART, USB) on the row facing the module, 9-16 (DTR/RTS) facing the USB-A")

# ------------------------------------------------------------------ outputs
add("R17", "Device", "R", R0402, "1k", {"1": "SBUS_OUT", "2": "AUX_SBUS"}, "outputs", region="T5")
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

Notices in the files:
README.md:
License:
MIT, see [LICENSE](LICENSE). The `espressif/usb` and `espressif/usb_host_hid` components fetched
at build time are Apache-2.0.
License: MIT
- **Nothing reused from `USB_to_RC`** (RP2040 + PIO USB, GPL-3.0) beyond its architecture idea of
hardware/kicad/j2t-module.kicad_sch:
esp32-joystick2trainer (MIT firmware, CERN-OHL-P-2.0 hardware)
